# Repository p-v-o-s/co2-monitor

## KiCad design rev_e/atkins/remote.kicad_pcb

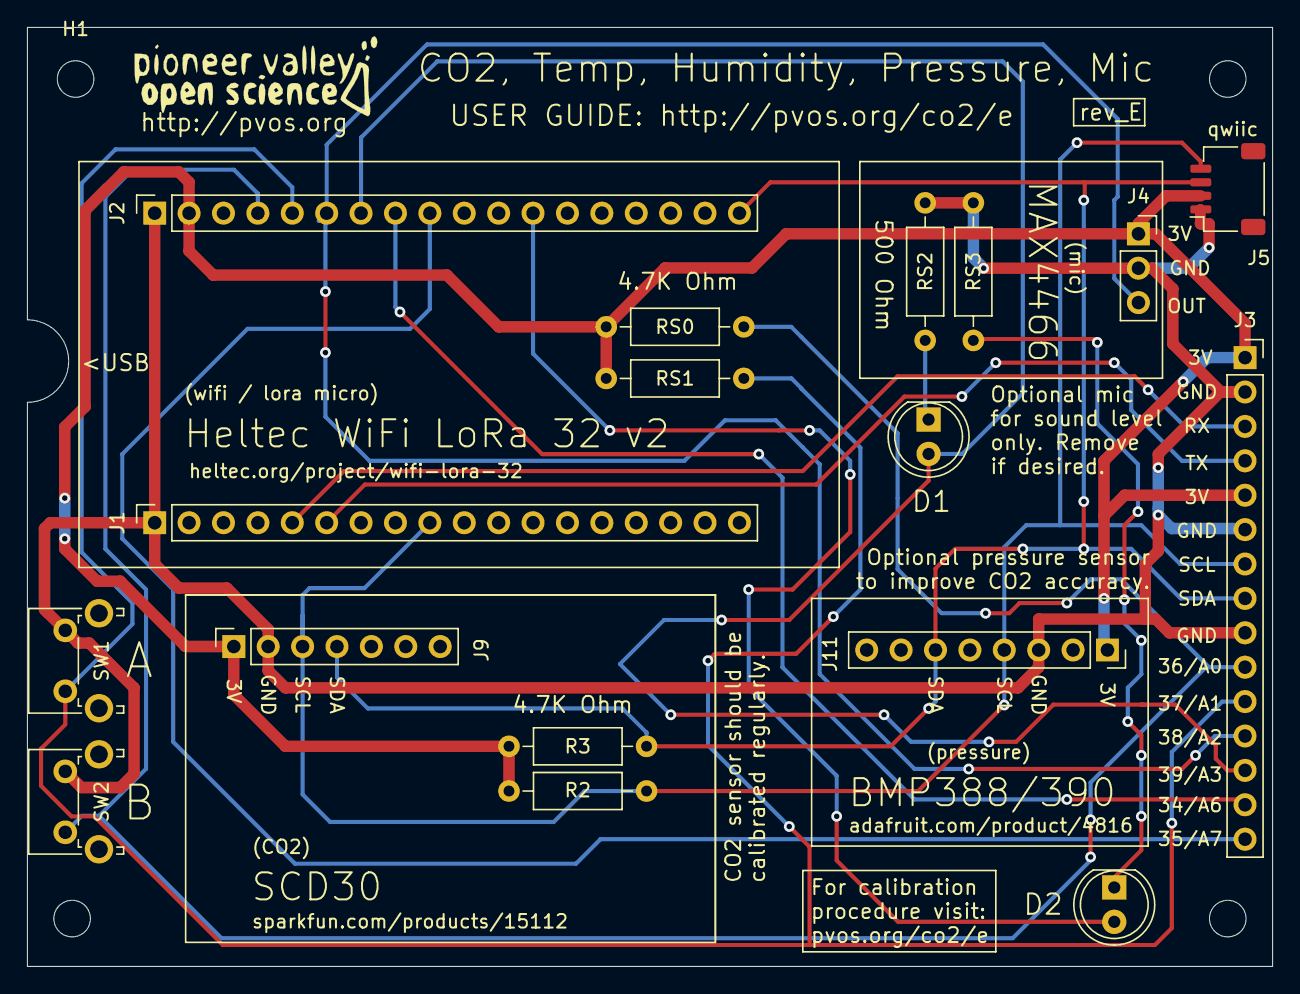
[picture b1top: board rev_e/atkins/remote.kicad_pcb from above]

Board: 2 copper layers, 91.9 x 69.3 mm, 21 parts (0 on the bottom side), 15 nets.

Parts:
D1, D2: LED; LED_D5.0mm
H1, H2, H3, H4: MountingHole; MountingHole_2.7mm_M2.5
J1, J2: Conn_01x18_Female; PinSocket_1x18_P2.54mm_Vertical
J3: Conn_01x15_Female; PinSocket_1x15_P2.54mm_Vertical
J4: Conn_01x03_Female; PinSocket_1x03_P2.54mm_Vertical
J5: Conn_01x04_Female; JST_SH_SM04B-SRSS-TB_1x04-1MP_P1.00mm_Horizontal
J9: SCD30; PinSocket_1x07_P2.54mm_Vertical
J11: BME390; PinSocket_1x08_P2.54mm_Vertical
R2, R3: R; R_Axial_DIN0207_L6.3mm_D2.5mm_P10.16mm_Horizontal
RS0, RS1: 10K; R_Axial_DIN0207_L6.3mm_D2.5mm_P10.16mm_Horizontal
RS2, RS3: 500R; R_Axial_DIN0207_L6.3mm_D2.5mm_P10.16mm_Horizontal
SW1, SW2: SW_Push; SW_Tactile_SPST_Angled_PTS645Vx58-2LFS

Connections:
25_LED: D2.2, J2.12
34_A6: J2.8, J3.14
35_A7: J2.9, J3.15
36_A0: J2.4, J3.10, RS0.2, SW2.1
37_A1: J2.5, J3.11, RS1.2, SW1.1
38_A2: J2.6, J3.12, J4.3
39_A3: D1.2, J2.7, J3.13
+3V3: J2.2, J3.1, J3.5, J4.1, J5.2, J9.1, J11.1, R2.1, R3.1, RS0.1, RS1.1
GND: J1.1, J2.1, J3.2, J3.6, J3.9, J4.2, J5.1, J9.2, J11.3, RS2.2, RS3.2, SW1.2, SW2.2
unnamed: D1.1, RS2.1
unnamed: D2.1, RS3.1
RX: J1.5, J3.3
SCL: J1.9, J3.7, J5.4, J9.3, J11.4, R2.2
SDA: J2.18, J3.8, J5.3, J9.4, J11.6, R3.2
TX: J1.6, J3.4

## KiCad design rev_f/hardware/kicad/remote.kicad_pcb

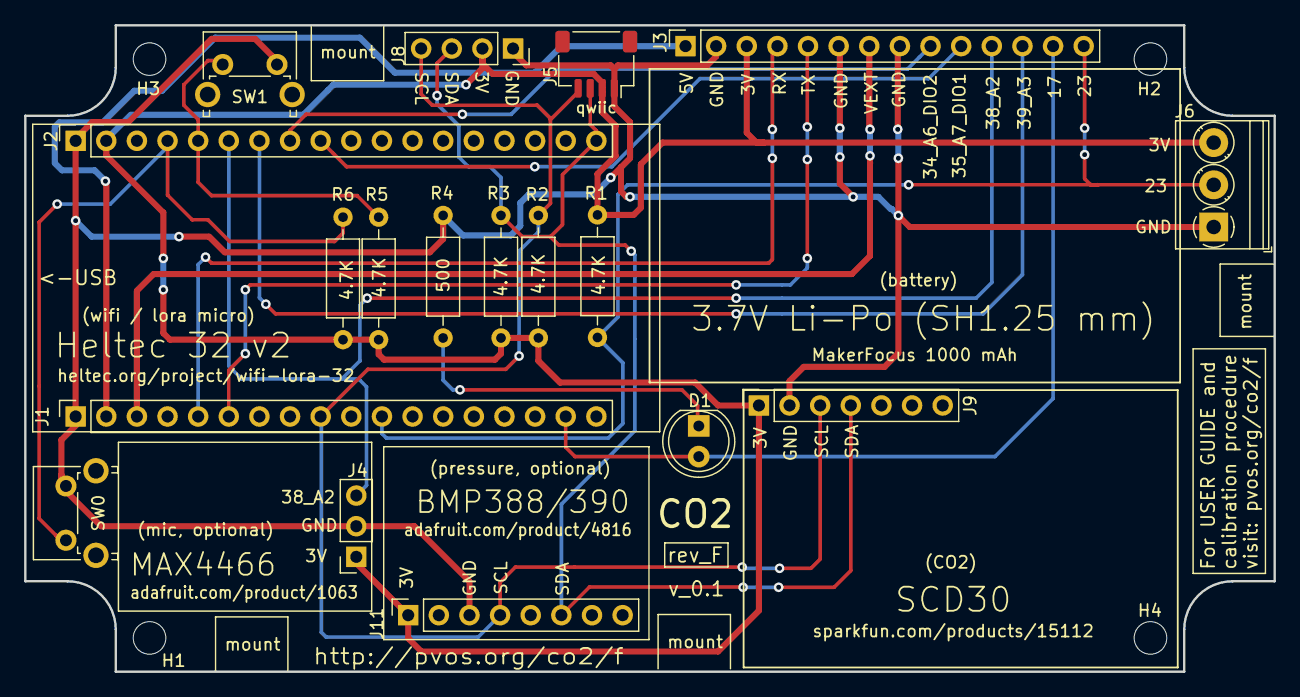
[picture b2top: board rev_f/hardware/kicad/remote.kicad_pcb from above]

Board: 2 copper layers, 103.6 x 53.6 mm, 22 parts (0 on the bottom side), 17 nets.

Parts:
D1: LED; LED_D5.0mm
H1, H2, H3, H4: MountingHole; MountingHole_2.7mm_M2.5
J1, J2: Conn_01x18_Female; PinSocket_1x18_P2.54mm_Vertical
J3: Conn_01x14_Female; PinSocket_1x14_P2.54mm_Vertical
J4: Conn_01x03_Female; PinSocket_1x03_P2.54mm_Vertical
J5: Conn_01x04_Female; JST_SH_SM04B-SRSS-TB_1x04-1MP_P1.00mm_Horizontal
J6: Screw_Terminal_01x03; TerminalBlock_Phoenix_PT-1,5-3-3.5-H_1x03_P3.50mm_Horizontal
J8: Conn_01x04_Female; PinSocket_1x04_P2.54mm_Vertical
J9: SCD30; PinSocket_1x07_P2.54mm_Vertical
J11: BME390; PinSocket_1x08_P2.54mm_Vertical
R1, R2, R3: R; R_Axial_DIN0207_L6.3mm_D2.5mm_P10.16mm_Horizontal
R4: 500R; R_Axial_DIN0207_L6.3mm_D2.5mm_P10.16mm_Horizontal
R5, R6: 4.7K; R_Axial_DIN0207_L6.3mm_D2.5mm_P10.16mm_Horizontal
SW0, SW1: SW_Push; SW_Tactile_SPST_Angled_PTS645Vx58-2LFS

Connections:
5V: J1.2, J3.1
17: D1.2, J1.17, J3.13
23: J1.11, J3.14, J6.2, R1.2
34_ADC6_DIO2: J2.8, J3.9
35_ADC7_DIO1: J2.9, J3.10
36_A0: J2.4, R6.2, SW0.1
37_A1: J2.5, R5.2, SW1.1
38_A2: J2.6, J3.11, J4.3
39_A3: J2.7, J3.12
+3V3: J2.2, J3.3, J4.1, J5.2, J6.3, J8.2, J9.1, J11.1, R1.1, R2.1, R3.1, R5.1, R6.1
GND: J1.1, J2.1, J3.2, J3.6, J3.8, J4.2, J5.1, J6.1, J8.1, J9.2, J11.3, R4.2, SW0.2, SW1.2
unnamed: D1.1, R4.1
RX: J1.5, J3.4
SCL: J1.9, J5.4, J8.4, J9.3, J11.4, R2.2
SDA: J2.18, J5.3, J8.3, J9.4, J11.6, R3.2
TX: J1.6, J3.5
VEXT: J1.3, J3.7

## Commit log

2021-01-15 got basic measurements working
2021-01-16 added random number; still working on loading parameters
2021-01-16 added actual CO2 monitoring code! getting closer ...
2021-01-18 added some directories
2021-01-18 cleaned up base code
2021-01-18 more cleanup
2021-01-18 reading in param file now, displaying co2 to screen
2021-01-18 increased font size
2021-01-18 show network config on button press
2021-01-19 printint out free heap; some string improvements (but should switch to char); works, but no resolution of observed wifi issue as yet
2021-01-19 added calibration procedure
2021-01-19 fixed interface bug
2021-01-20 working code, but fragile regarding wifi connection loss.
2021-01-20 added restart code, using NAcounts variable
2021-01-24 added HTTP response code at top right, and IP address on connected wifi on bottom
2021-01-25 using fixed 5 minute measurement interval until can figure out how to load from parameters
2021-01-25 fixed bug in httpcode display as ip
2021-01-25 fixed display bug
